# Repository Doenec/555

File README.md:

# 555
open source hardware with the classic 555

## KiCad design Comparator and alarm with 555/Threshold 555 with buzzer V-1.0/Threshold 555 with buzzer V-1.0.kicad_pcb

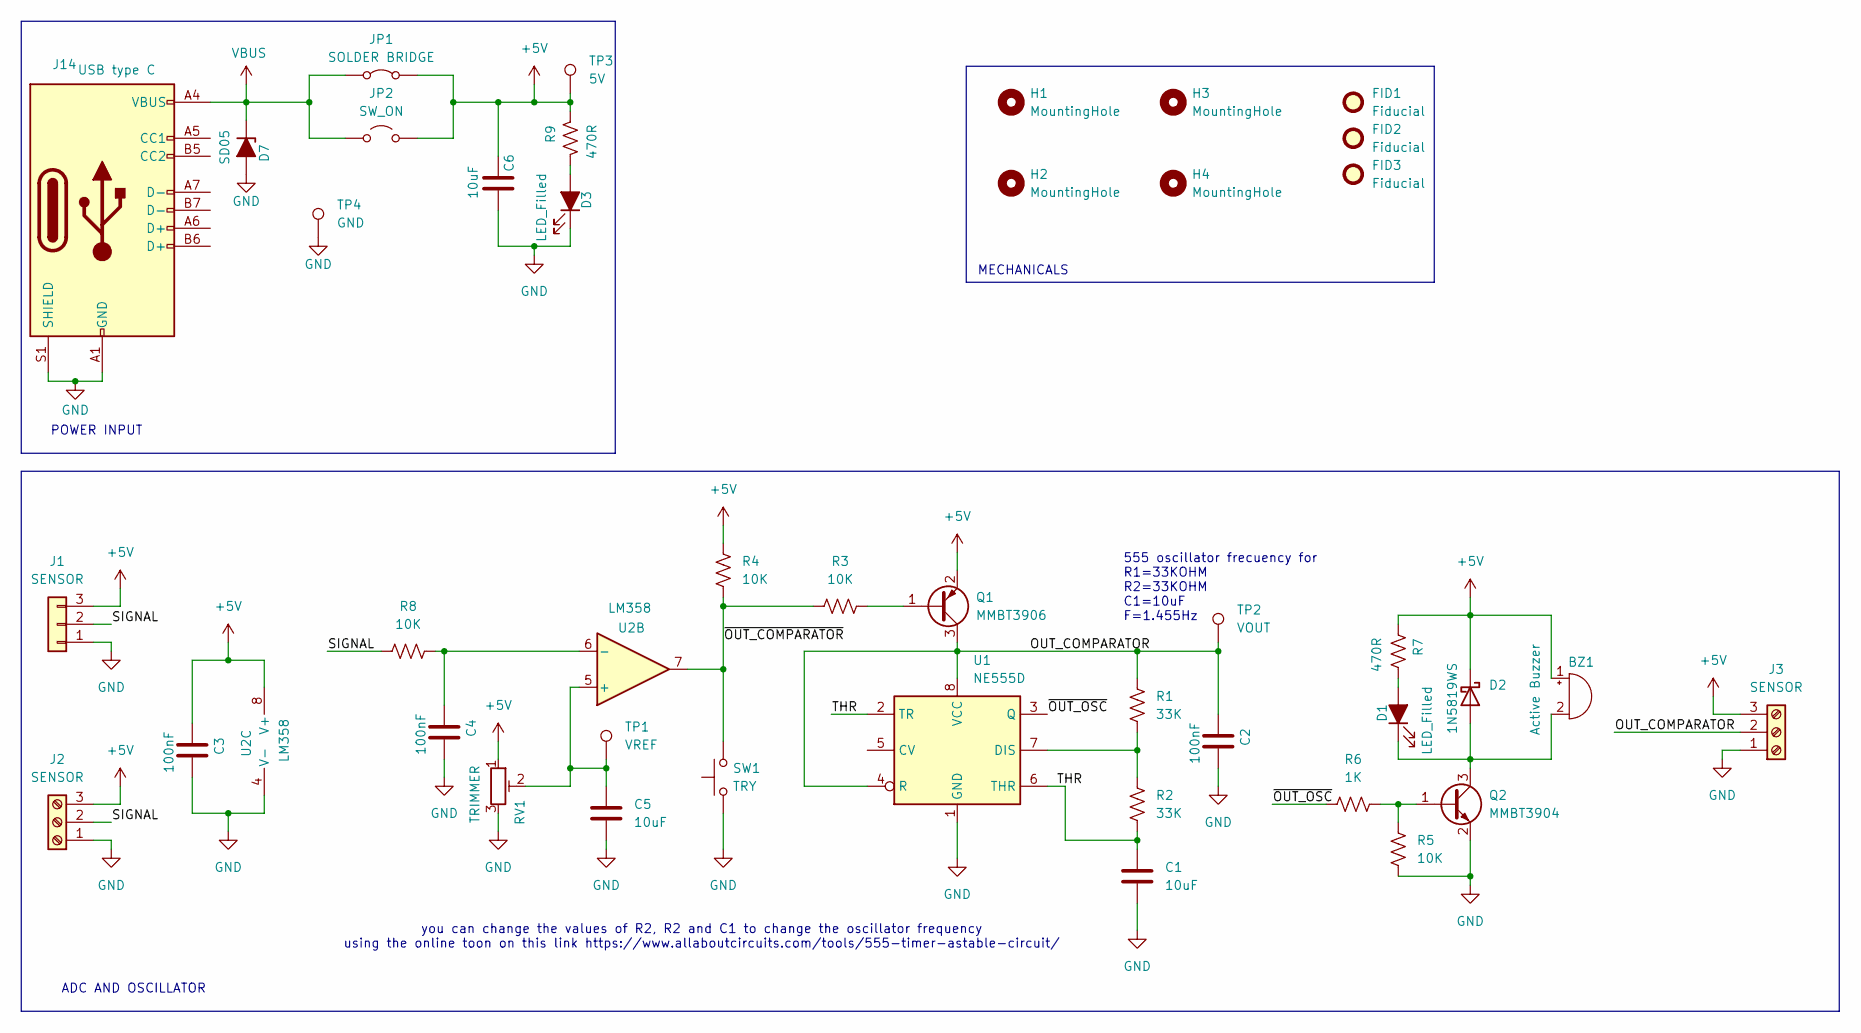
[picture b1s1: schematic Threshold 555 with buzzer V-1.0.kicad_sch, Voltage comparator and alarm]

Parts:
BZ1: Active Buzzer; Buzzer_12x9.5RM7.6
C1, C5, C6: 10uF; C_1206_3216Metric_Pad1.33x1.80mm_HandSolder
C2, C3, C4: 100nF; C_1206_3216Metric_Pad1.33x1.80mm_HandSolder
D1, D3: LED_Filled; LED_1206_3216Metric_Pad1.42x1.75mm_HandSolder
D2: 1N5819WS; D_SOD-323
D7: SD05; D_SOD-323; MPN SD05; LCSC-PN C502527
FID1, FID2, FID3: Fiducial; Fiducial_0.5mm_Mask1mm
H1, H2, H3, H4: MountingHole; MountingHole_3.2mm_M3
J1: SENSOR; JST_XH_S3B-XH-A_1x03_P2.50mm_Horizontal
J2, J3: SENSOR; TerminalBlock_Phoenix_MKDS-1,5-3-5.08_1x03_P5.08mm_Horizont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
J14: USB type C; USB_C_Receptacle_HRO_TYPE-C-31-M-12; MPN TYPE-C-31-M-12; LCSC-PN C165948
JP1: SOLDER BRIDGE; SolderJumper-2_P1.3mm_Bridged_RoundedPad1.0x1.5mm
JP2: SW_ON; PinHeader_1x02_P2.54mm_Vertical
Q1: MMBT3906; SOT-23
Q2: MMBT3904; SOT-23
R1, R2: 33K; R_1206_3216Metric_Pad1.30x1.75mm_HandSolder
R3, R4, R5, R8: 10K; R_1206_3216Metric_Pad1.30x1.75mm_HandSolder
R6: 1K; R_1206_3216Metric_Pad1.30x1.75mm_HandSolder
R7, R9: 470R; R_1206_3216Metric_Pad1.30x1.75mm_HandSolder
RV1: TRIMMER; Potentiometer_Runtron_RM-065_Vertical
SW1: TRY; SW_PUSH_6mm
TP1: VREF; TestPoint_Pad_D1.5mm
TP2: VOUT; TestPoint_Pad_D1.5mm
TP3: 5V; TestPoint_Pad_D1.5mm
TP4: GND; TestPoint_Pad_D1.5mm
U1: NE555D; SOIC-8_3.9x4.9mm_P1.27mm
U2: LM358; SOIC-8_3.9x4.9mm_P1.27mm

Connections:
+5V: BZ1.1 (+), C3.1, C6.1, D2.1 (K), J1.3, J2.3, J3.3, JP1.2 (B), JP2.2 (B), Q1.2 (E), R4.2, R7.2, R9.2, RV1.1, TP3.1, U2.8 (V+)
/OUT_COMPARATOR: C2.1, J3.2, Q1.3 (C), R1.1, TP2.1, U1.4 (R), U1.8 (VCC)
/SIGNAL: J1.2, J2.2, R8.2
/THR: C1.1, R2.2, U1.2 (TR), U1.6 (THR)
/~OUT_COMPARATOR: R3.1, R4.1, SW1.2, U2.7
/~OUT_OSC: R6.2, U1.3 (Q)
GND: C1.2, C2.2, C3.2, C4.2, C5.2, C6.2, D3.1 (K), D7.2 (A), J1.1, J2.1, J3.1, J14.A1 (GND), J14.A12 (GND), J14.B1 (GND), J14.B12 (GND), J14.S1 (SHIELD), Q2.2 (E), R5.1, RV1.3, SW1.1, TP4.1, U1.1 (GND), U2.4 (V-)
unnamed: BZ1.2 (-), D1.1 (K), D2.2 (A), Q2.3 (C)
unnamed: D1.2 (A), R7.1
unnamed: D3.2 (A), R9.1
unnamed: Q1.1 (B), R3.2
unnamed: Q2.1 (B), R5.2, R6.1
unnamed: R1.2, R2.1, U1.7 (DIS)
unnamed: C5.1, RV1.2, TP1.1, U2.5 (+)
unnamed: C4.1, R8.1, U2.6 (-)
VBUS: D7.1 (K), J14.A4 (VBUS), J14.A9 (VBUS), J14.B4 (VBUS), J14.B9 (VBUS), JP1.1 (A), JP2.1 (A)

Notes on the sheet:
ADC AND OSCILLATOR
555 oscillator frecuency for R1=33KOHM R2=33KOHM C1=10uF F=1.455Hz
POWER INPUT
you can change the values of R2, R2 and C1 to change the oscillator frequency using the online toon on this link https://www.allaboutcircuits.com/tools/555-timer-astable-circuit/
MECHANICALS

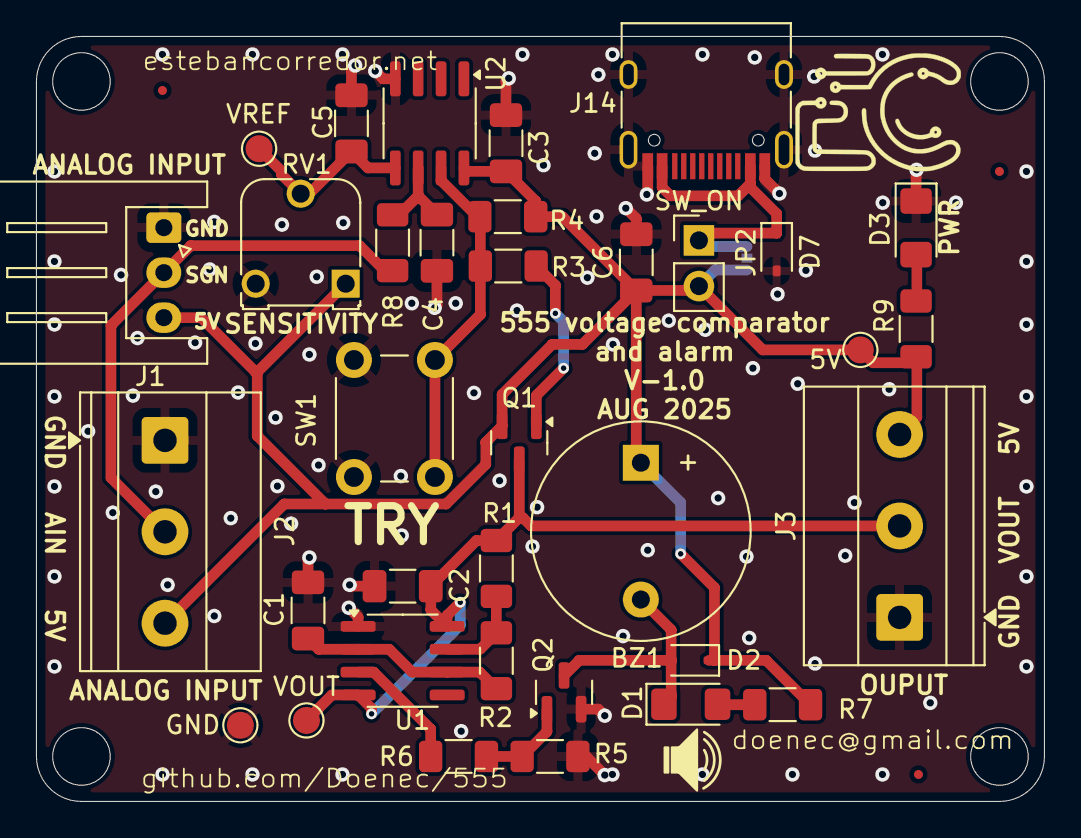
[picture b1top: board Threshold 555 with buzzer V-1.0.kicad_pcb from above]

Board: 2 copper layers, 56.0 x 42.5 mm, 43 parts (1 on the bottom side), 16 nets.

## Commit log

2025-08-03 555 alarm
